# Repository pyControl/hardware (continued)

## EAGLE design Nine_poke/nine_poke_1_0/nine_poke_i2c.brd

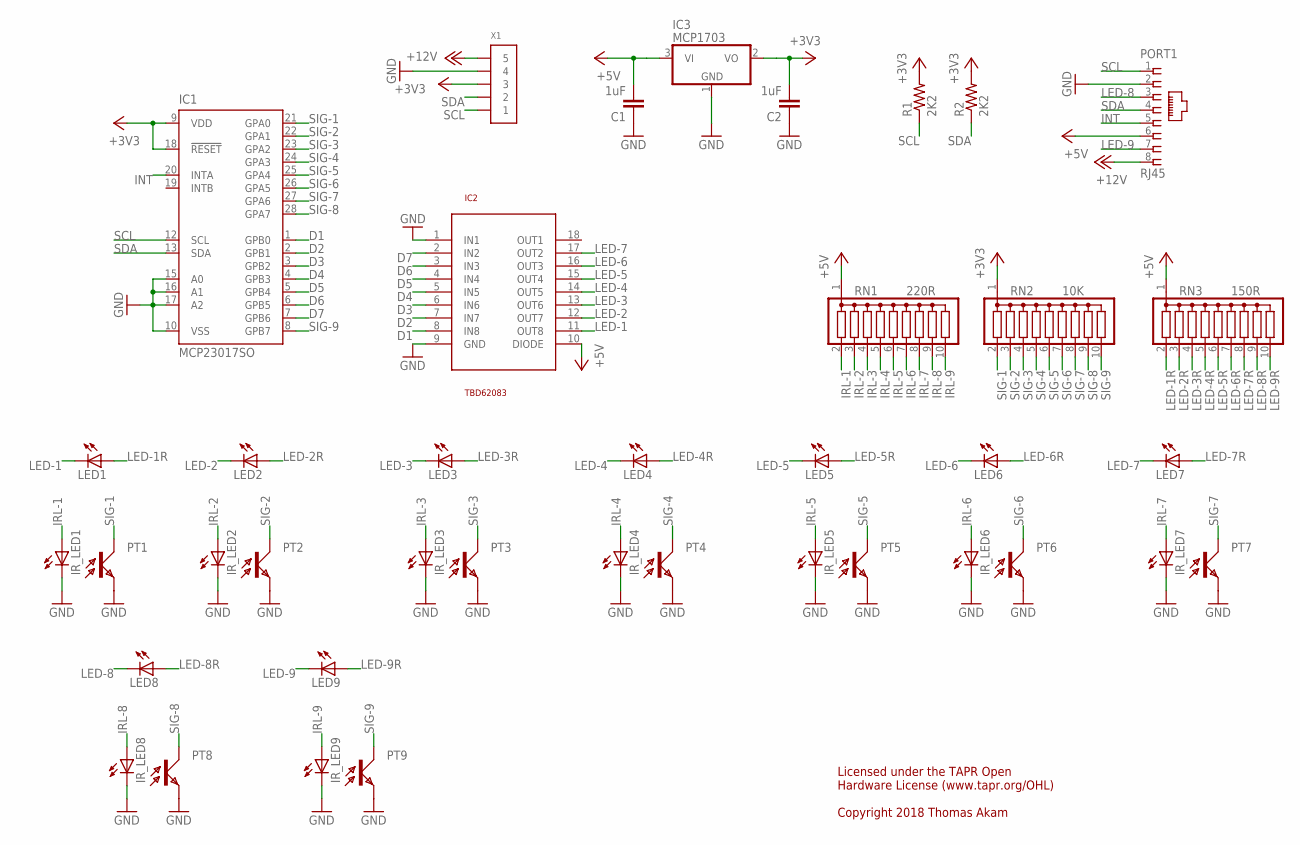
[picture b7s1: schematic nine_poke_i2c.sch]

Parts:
C1, C2: 1uF; C0805
IC1: MCP23017SO; SO28W
IC2: TBD62083; SO18L
IC3: MCP1703; SOT23
IR_LED1, IR_LED2, IR_LED3, IR_LED4, IR_LED5, IR_LED6, IR_LED7, IR_LED8, IR_LED9: LEDIRL80A; IRL80A
LED1, LED2, LED3, LED4, LED5, LED6, LED7, LED8, LED9: LEDSML0805; SML0805
PORT1: RJ45; RJ45-NO-SHIELD-VERTICAL
PT1, PT2, PT3, PT4, PT5, PT6, PT7, PT8, PT9: LPT80A
R1, R2: 2K2; 0805
RN1: 220R; SIL10
RN2: 10K; SIL10
RN3: 150R; SIL10
X1: CONN_5-1-53398; PB-53398-05

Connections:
+3V3: C2.2, IC1.9 (VDD), IC1.18 (!RESET), IC3.2 (VO), R1.2, R2.2, RN2.1, X1.3
+5V: C1.2, IC2.10 (DIODE), IC3.3 (VI), PORT1.6, RN1.1, RN3.1
+12V: PORT1.8, X1.5
D1: IC1.1 (GPB0), IC2.8 (IN8)
D2: IC1.2 (GPB1), IC2.7 (IN7)
D3: IC1.3 (GPB2), IC2.6 (IN6)
D4: IC1.4 (GPB3), IC2.5 (IN5)
D5: IC1.5 (GPB4), IC2.4 (IN4)
D6: IC1.6 (GPB5), IC2.3 (IN3)
D7: IC1.7 (GPB6), IC2.2 (IN2)
GND: C1.1, C2.1, IC1.10 (VSS), IC1.15 (A0), IC1.16 (A1), IC1.17 (A2), IC2.1 (IN1), IC2.9 (GND), IC3.1 (GND), IR_LED1.K (C), IR_LED2.K (C), IR_LED3.K (C), IR_LED4.K (C), IR_LED5.K (C), IR_LED6.K (C), IR_LED7.K (C), IR_LED8.K (C), IR_LED9.K (C), PORT1.2, PT1.E, PT2.E, PT3.E, PT4.E, PT5.E, PT6.E, PT7.E, PT8.E, PT9.E, X1.4
INT: IC1.20 (INTA), PORT1.5
IRL-1: IR_LED1.A, RN1.2
IRL-2: IR_LED2.A, RN1.3
IRL-3: IR_LED3.A, RN1.4
IRL-4: IR_LED4.A, RN1.5
IRL-5: IR_LED5.A, RN1.6
IRL-6: IR_LED6.A, RN1.7
IRL-7: IR_LED7.A, RN1.8
IRL-8: IR_LED8.A, RN1.9
IRL-9: IR_LED9.A, RN1.10
LED-1: IC2.11 (OUT8), LED1.C
LED-1R: LED1.A, RN3.2
LED-2: IC2.12 (OUT7), LED2.C
LED-2R: LED2.A, RN3.3
LED-3: IC2.13 (OUT6), LED3.C
LED-3R: LED3.A, RN3.4
LED-4: IC2.14 (OUT5), LED4.C
LED-4R: LED4.A, RN3.5
LED-5: IC2.15 (OUT4), LED5.C
LED-5R: LED5.A, RN3.6
LED-6: IC2.16 (OUT3), LED6.C
LED-6R: LED6.A, RN3.7
LED-7: IC2.17 (OUT2), LED7.C
LED-7R: LED7.A, RN3.8
LED-8: LED8.C, PORT1.3
LED-8R: LED8.A, RN3.9
LED-9: LED9.C, PORT1.7
LED-9R: LED9.A, RN3.10
SCL: IC1.12 (SCL), PORT1.1, R1.1, X1.1
SDA: IC1.13 (SDA), PORT1.4, R2.1, X1.2
SIG-1: IC1.21 (GPA0), PT1.C, RN2.2
SIG-2: IC1.22 (GPA1), PT2.C, RN2.3
SIG-3: IC1.23 (GPA2), PT3.C, RN2.4
SIG-4: IC1.24 (GPA3), PT4.C, RN2.5
SIG-5: IC1.25 (GPA4), PT5.C, RN2.6
SIG-6: IC1.26 (GPA5), PT6.C, RN2.7
SIG-7: IC1.27 (GPA6), PT7.C, RN2.8
SIG-8: IC1.28 (GPA7), PT8.C, RN2.9
SIG-9: IC1.8 (GPB7), PT9.C, RN2.10

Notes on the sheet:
Licensed under the TAPR Open Hardware License (www.tapr.org/OHL) Copyright 2018 Thomas Akam

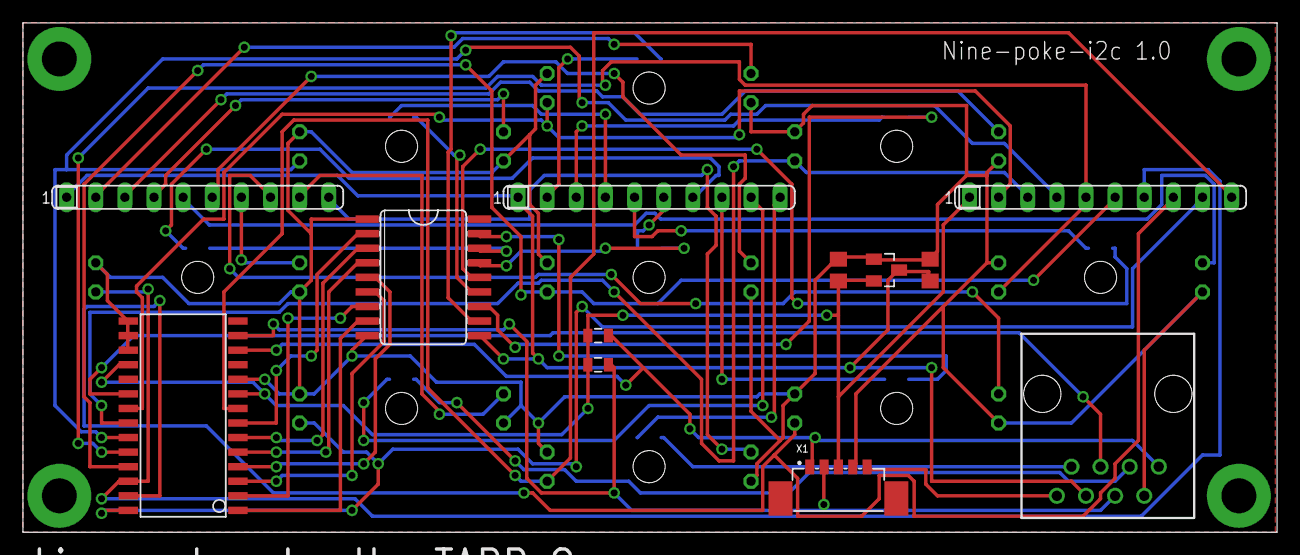
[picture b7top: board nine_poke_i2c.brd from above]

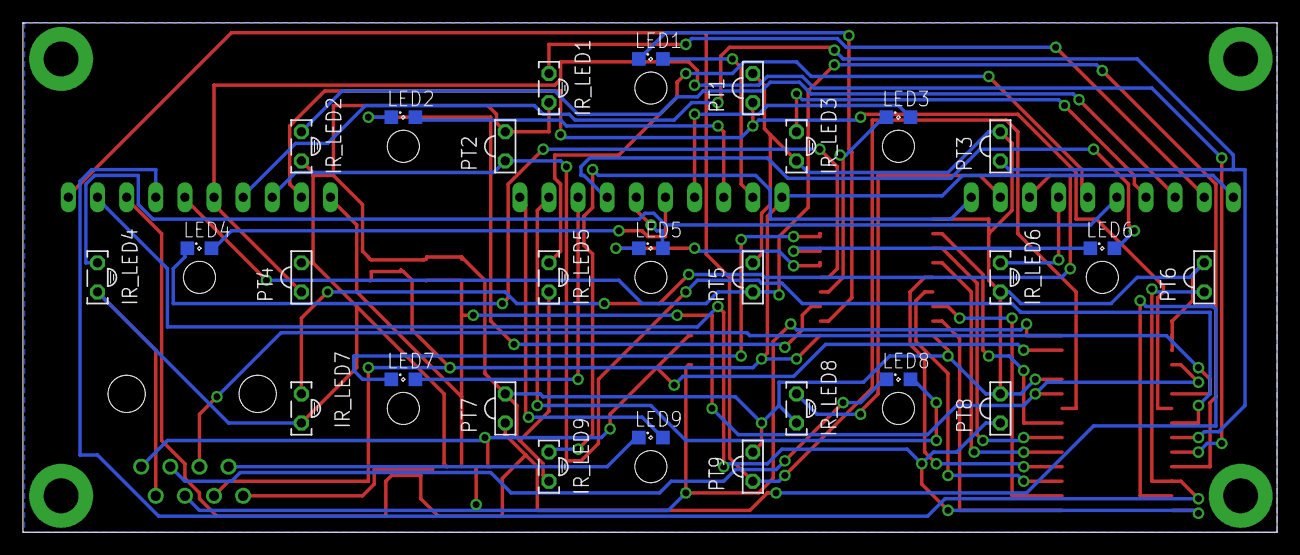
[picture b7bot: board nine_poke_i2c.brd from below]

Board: 2 copper layers, 109.4 x 44.4 mm, 39 parts (27 on the bottom side), 50 nets.

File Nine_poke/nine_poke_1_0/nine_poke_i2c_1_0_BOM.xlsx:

Part | Value | Device | Package | Description | MF | MPN | OC_FARNELL
IR_LED1 |  | - | - | IR LED side | Sharp | GL480E00000F | 9707794
IR_LED2 |  | - | - | IR LED side | Sharp | GL480E00000F | 9707794
IR_LED3 |  | - | - | IR LED side | Sharp | GL480E00000F | 9707794
IR_LED4 |  | - | - | IR LED side | Sharp | GL480E00000F | 9707794
IR_LED5 |  | - | - | IR LED side | Sharp | GL480E00000F | 9707794
IR_LED6 |  | - | - | IR LED side | Sharp | GL480E00000F | 9707794
IR_LED7 |  | - | - | IR LED side | Sharp | GL480E00000F | 9707794
IR_LED8 |  | - | - | IR LED side | Sharp | GL480E00000F | 9707794
IR_LED9 |  | - | - | IR LED side | Sharp | GL480E00000F | 9707794
LED1 |  | - | 0805 | LED white 0805 | MULTICOMP | OVS-0801 | 1716764
LED2 |  | - | 0805 | LED white 0805 | MULTICOMP | OVS-0801 | 1716764
LED3 |  | - | 0805 | LED white 0805 | MULTICOMP | OVS-0801 | 1716764
LED4 |  | - | 0805 | LED white 0805 | MULTICOMP | OVS-0801 | 1716764
LED5 |  | - | 0805 | LED white 0805 | MULTICOMP | OVS-0801 | 1716764
LED6 |  | - | 0805 | LED white 0805 | MULTICOMP | OVS-0801 | 1716764
LED7 |  | - | 0805 | LED white 0805 | MULTICOMP | OVS-0801 | 1716764
LED8 |  | - | 0805 | LED white 0805 | MULTICOMP | OVS-0801 | 1716764
LED9 |  | - | 0805 | LED white 0805 | MULTICOMP | OVS-0801 | 1716764
PT1 |  | - | - | PHOTO TRANSISTOR | OSRAM | SFH3100F-1-Z | 1226443
PT2 |  | - | - | PHOTO TRANSISTOR | OSRAM | SFH3100F-1-Z | 1226443
PT3 |  | - | - | PHOTO TRANSISTOR | OSRAM | SFH3100F-1-Z | 1226443
PT4 |  | - | - | PHOTO TRANSISTOR | OSRAM | SFH3100F-1-Z | 1226443
PT5 |  | - | - | PHOTO TRANSISTOR | OSRAM | SFH3100F-1-Z | 1226443
PT6 |  | - | - | PHOTO TRANSISTOR | OSRAM | SFH3100F-1-Z | 1226443
PT7 |  | - | - | PHOTO TRANSISTOR | OSRAM | SFH3100F-1-Z | 1226443
PT8 |  | - | - | PHOTO TRANSISTOR | OSRAM | SFH3100F-1-Z | 1226443
PT9 |  | - | - | PHOTO TRANSISTOR | OSRAM | SFH3100F-1-Z | 1226443
RN1 | 220R | G09R | SIL10 | Resistor network | RESISTOR | 4610X-101-221LF | 9357165
RN2 | 10K | G09R | SIL10 | Resistor network | BOURNS | 4610X-101-103LF | 9357122
RN3 | 150R | G09R | SIL10 | Resistor network | RESISTOR | 4610X-101-151LF | -
PORT1 |  | - | - | RJ45VERTICAL | TE CONNECTIVITY | 5556416-1 | 1773034
R1 | 2K2 | - | 0805 | Resistor 0805 | Multicomp | MCWR08X2201FTL | 2447623
R2 | 2K2 | - | 0805 | Resistor 0805 | Multicomp | MCWR08X2201FTL | 2447623
C1 | 1uF | - | 0805 | capacitor 0805 | Multicomp | MC0805B105K250CT | 2320827
C2 | 1uF | - | 0805 | capacitor 0805 | Multicomp | MC0805B105K250CT | 2320827
IC1 | - | MCP23017 | SO28 | i2c port expander | MICROCHIP | MCP23017-E/SO | 1332087
IC2 |  | TBD62083 | SO18 | Low side driver | Toshiba | TBD62083AFG | -
IC3 | - | MCP1703T | SOT-23 | Voltage regulator 3v3 | MICROCHIP | MCP1703T-3302E/CB | 1439518
X1 | - | - | - | PicoBlade connector | MOLEX | 53398-0571 | 1125354
